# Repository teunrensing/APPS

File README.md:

# APPS

Dit is de repository met alle firmware- (source code), hardware- (kicad+schematische tekening) en GUI ontwerp bestanden (squareline studio) gemaakt door de S3 groep van 2022/2023.
De firmware is geschreven in c en maakt gebruik van het esp-idf framework. Esp-idf is een framework wat los geinstalleerd moet worden en niet meegeleverd wordt met een IDE.

VSCode in combinatie met de c/c++ en c/c++ extension pack is het makkelijkst op te zetten. Voor een handleiding [klik hier](https://github.com/teunrensing/APPS/tree/main/docs/install_vscode.md)
De hardware ontwerpbestanden zijn gemaakt in kicad, er staat nog een actuele PDF van de schematische tekening in de GitHub repo.

De GUI ontwerpbestanden zijn gemaakt in squareline studio. (Let op! In autogegenereerde .c bestanden van squareline studio wordt schaduw gebruikt. Dit onderdeel werkt niet en laat de ESP32 crashen. Verwijder deze stukjes code bij het porten van de code naar de ESP32.)

## Status Hardware
De hardware functioneert. Er zijn wat kleine foutjes. Zo zijn de ID_RES pullup weerstanden verkeerd getekend. En zijn niet alle modules precies zoals ze zouden moeten zijn.
Mocht iemand zin hebben om een volgende versie te maken... hier wat tips:
- Gebruik grotere onderdelen (geen mssop flipflop)
- Haal het flipflop flankdetectie circuit eruit voor de encoder
- Maak gebruik van een ESP32 devboard i.p.v. een esp32-wroom module
- Blijf gebruik maken van standaard onderdelen zoals: 74HC14 en 74HC595
- Haal de extra output en input pins weg. 
- Haal een hele boel switch input pins weg. 
- Haal de flat flex connector weg voor een display

## Status Software

Er zijn op dit moment drie volledige instelschermen (Licht, Vibratie en Tens) volledig af en functionerend. De code is nog vrij grof en lelijk. Dit kan flink gerefactord worden nog. 
- Er is een module driver voor licht en motor. **Maar de Tens driver ontbreekt nog.**
- Er is geen datacommunicatie protocol gemaakt voor externe communicatie met sensoren.
- Er is geen stuk software gemaakt die gebruik maakt van de microsd kaart slot.
- Er is geen stuk software die detecteert dat de noodstop is ingedrukt. Dit is op dit moment alleen in hardware afgehandeld.
- Er zijn geen unit testen (cmock of dut testen)

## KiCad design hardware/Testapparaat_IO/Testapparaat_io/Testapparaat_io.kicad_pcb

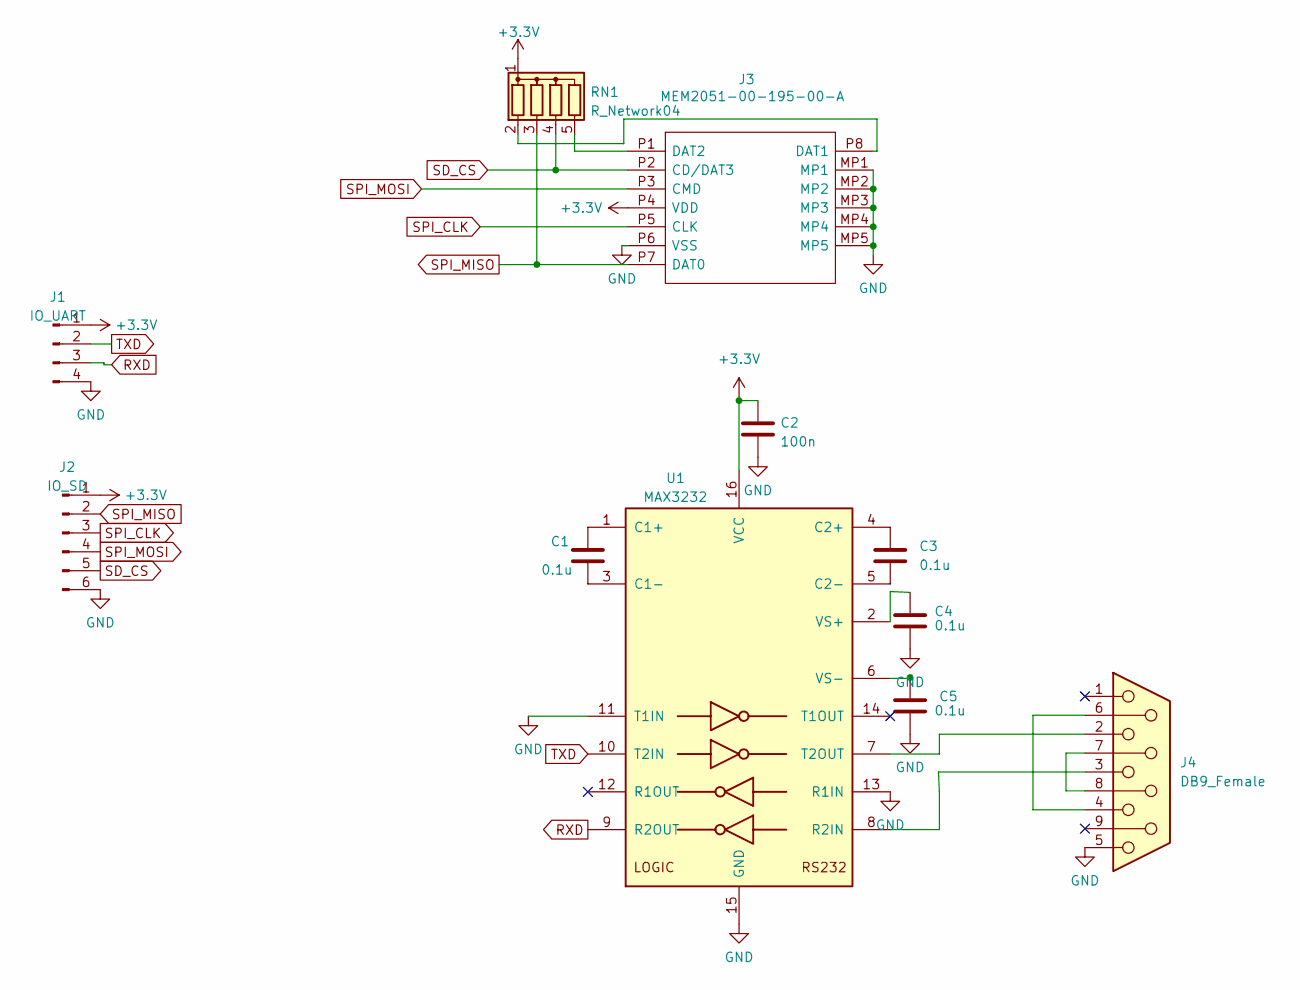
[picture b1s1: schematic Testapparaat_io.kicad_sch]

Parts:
C1, C3, C4, C5: 0.1u; C_0603_1608Metric_Pad1.08x0.95mm_HandSolder
C2: 100n; C_0603_1608Metric_Pad1.08x0.95mm_HandSolder
J1: IO_UART; PinHeader_1x04_P2.54mm_Horizontal
J2: IO_SD; PinHeader_1x06_P2.54mm_Horizontal
J3: MEM2051-00-195-00-A; MEM20510019500A; Manufacturer_Part_Number MEM2051-00-195-00-A; Mouser Part Number 640-MEM20510019500A
J4: DB9_Female; G17C0900132EU
RN1: R_Network04; R_Array_SIP5
U1: MAX3232; TSSOP-16_4.4x5mm_P0.65mm

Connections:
+3.3V: C2.1, J1.1, J2.1, J3.P4 (VDD), RN1.1 (common), U1.16 (VCC)
GND: C2.2, C4.1, C5.2, J1.4, J2.6, J3.MP1, J3.MP2, J3.MP3, J3.MP4, J3.MP5, J3.P6 (VSS), J4.5, U1.11 (T1IN), U1.13 (R1IN), U1.15 (GND)
unnamed: C1.1, U1.1 (C1+)
unnamed: C1.2, U1.3 (C1-)
unnamed: C3.1, U1.4 (C2+)
unnamed: C3.2, U1.5 (C2-)
unnamed: C4.2, U1.2 (VS+)
unnamed: C5.1, U1.6 (VS-)
unnamed: J3.P8 (DAT1), RN1.2 (R1)
unnamed: J4.2, U1.7 (T2OUT)
unnamed: J4.3, U1.8 (R2IN)
unnamed: J4.4, J4.6
unnamed: J4.7, J4.8
unnamed: J3.P1 (DAT2), RN1.5 (R4)
RXD: J1.3, U1.9 (R2OUT)
SD_CS: J2.5, J3.P2 (CD/DAT3), RN1.4 (R3)
SPI_CLK: J2.3, J3.P5 (CLK)
SPI_MISO: J2.2, J3.P7 (DAT0), RN1.3 (R2)
SPI_MOSI: J2.4, J3.P3 (CMD)
TXD: J1.2, U1.10 (T2IN)

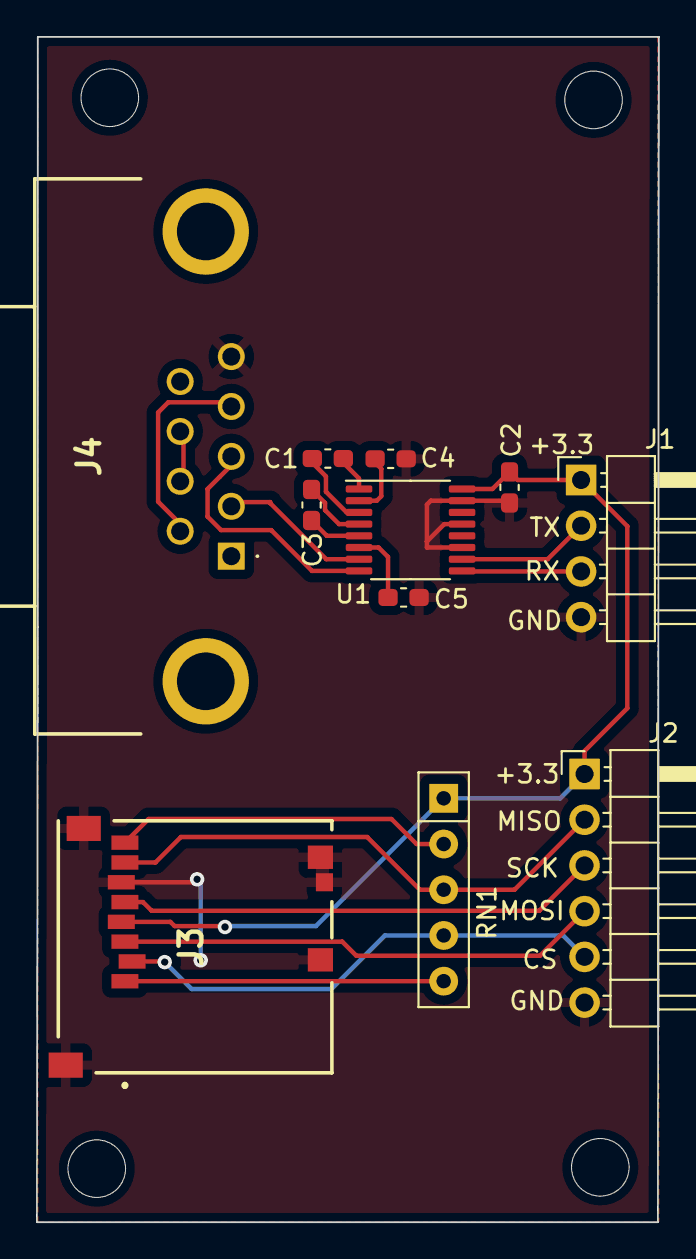
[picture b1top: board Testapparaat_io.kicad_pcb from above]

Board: 2 copper layers, 34.5 x 65.8 mm, 11 parts (0 on the bottom side), 20 nets.

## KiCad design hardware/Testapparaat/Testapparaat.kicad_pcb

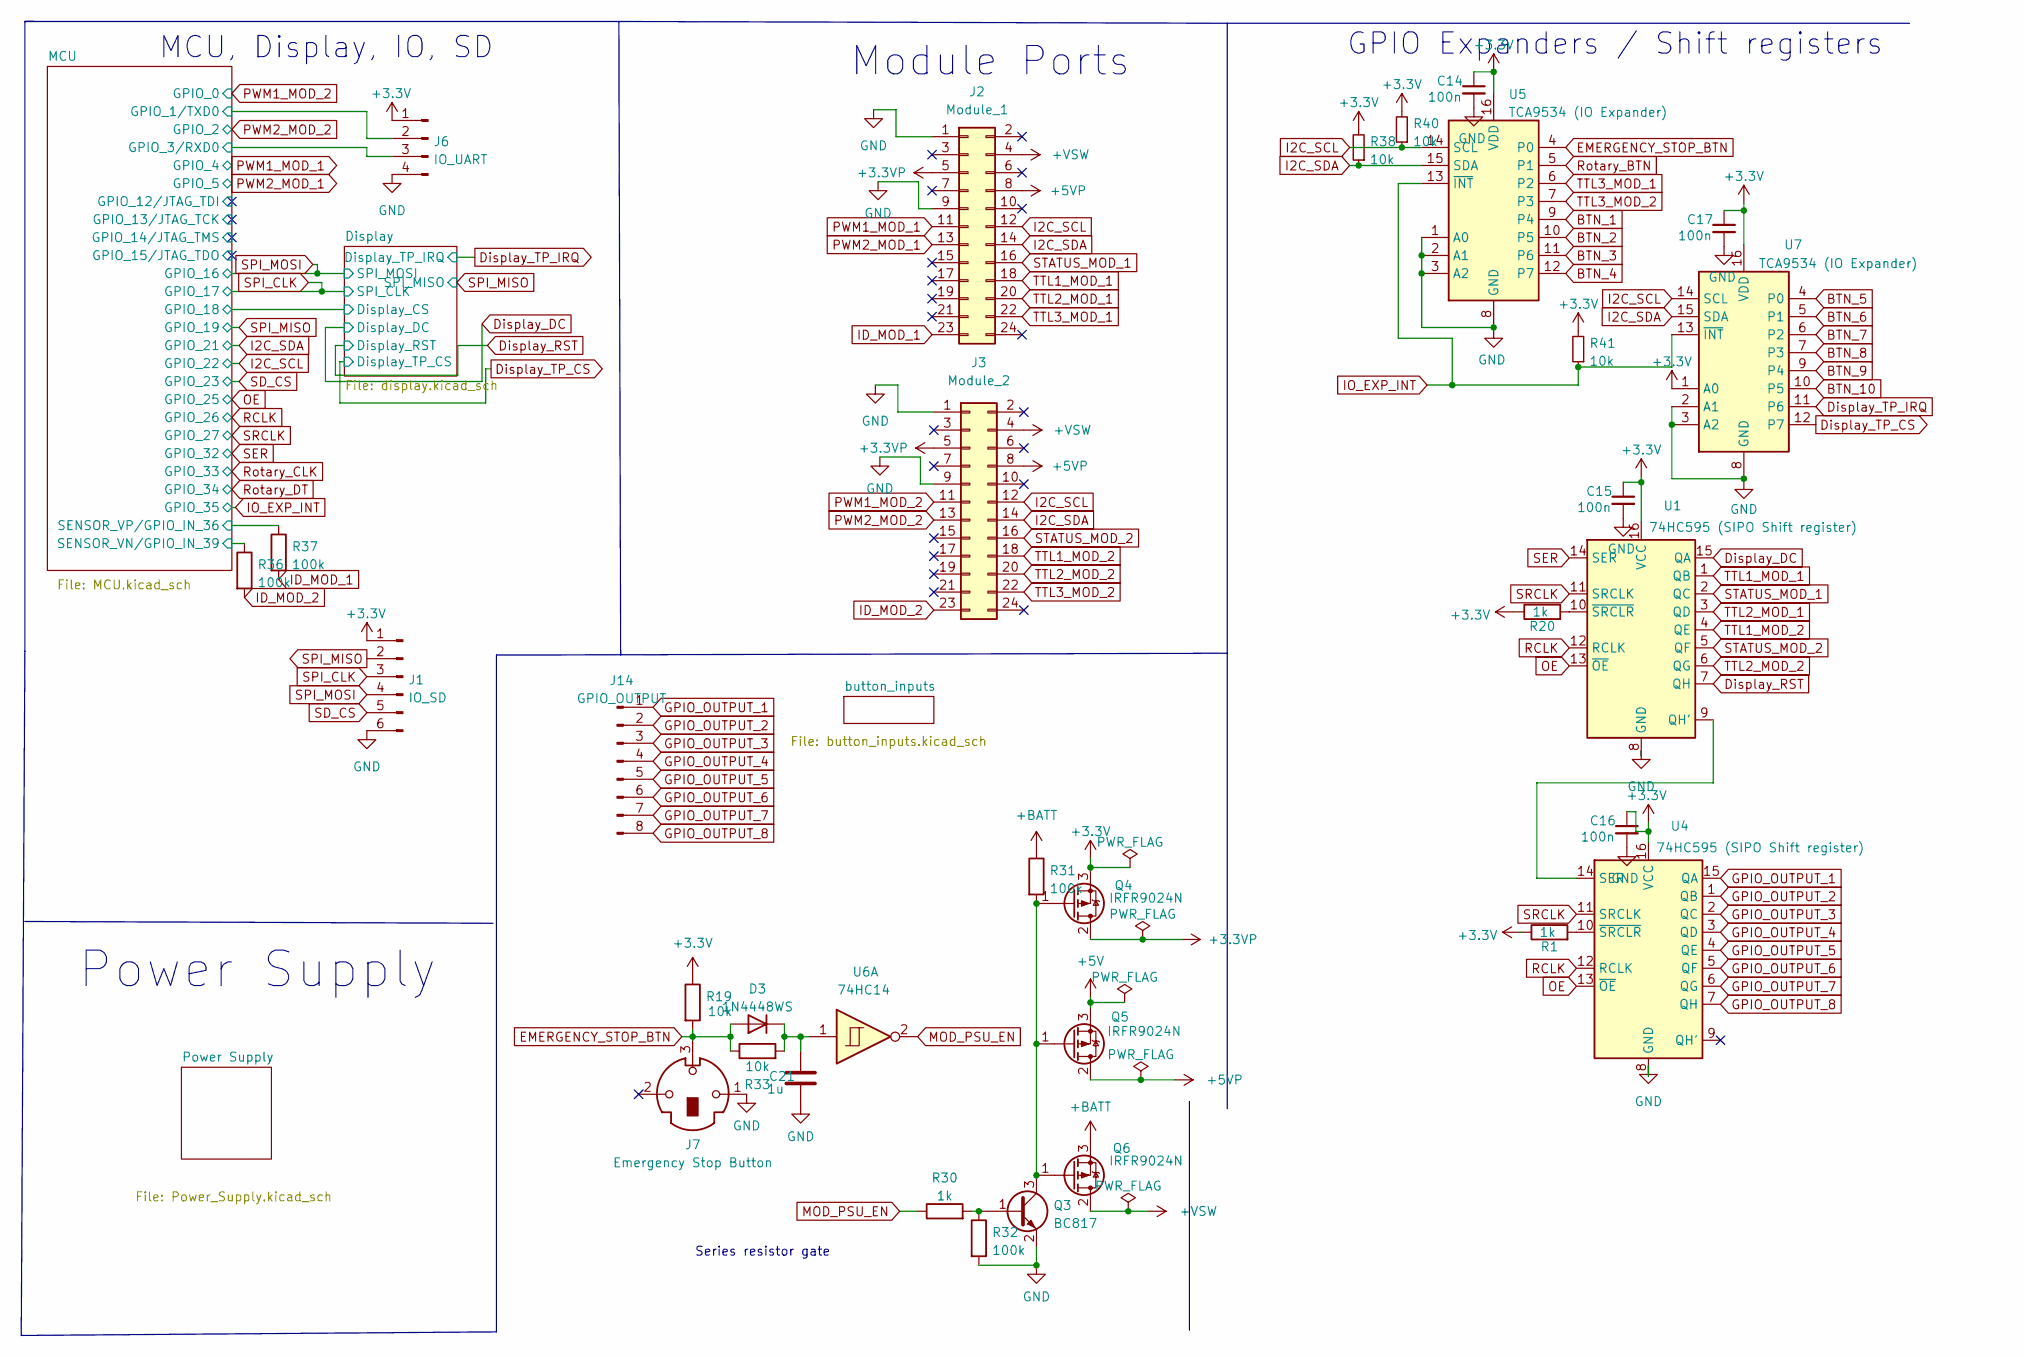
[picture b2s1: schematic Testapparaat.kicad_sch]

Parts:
C14, C15, C16, C17: 100n; C_0603_1608Metric_Pad1.08x0.95mm_HandSolder
C21: 1u; C_0603_1608Metric_Pad1.08x0.95mm_HandSolder
D3: 1N4448WS; D_SOD-323
J1: IO_SD; PinHeader_1x06_P2.54mm_Horizontal
J2: Module_1; PinHeader_2x12_P2.54mm_Horizontal
J3: Module_2; PinHeader_2x12_P2.54mm_Horizontal
J6: IO_UART; PinHeader_1x04_P2.54mm_Horizontal
J7: Emergency Stop Button; PinHeader_1x03_P2.54mm_Horizontal
J14: GPIO_OUTPUT; PinHeader_2x04_P2.54mm_Vertical_SMD
Q3: BC817; SOT-23
Q4, Q5, Q6: IRFR9024N; TO-252-3_TabPin2
R1, R20, R30: 1k; R_0603_1608Metric_Pad0.98x0.95mm_HandSolder
R19, R33, R38, R40, R41: 10k; R_0603_1608Metric_Pad0.98x0.95mm_HandSolder
R31, R32, R36, R37: 100k; R_0603_1608Metric_Pad0.98x0.95mm_HandSolder
U1, U4: 74HC595 (SIPO Shift register); 74HC595DQ100118
U5, U7: TCA9534 (IO Expander); SOP65P640X120-16N
U6: 74HC14; SO-14_3.9x8.65mm_P1.27mm

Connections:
+3.3V: C14.1, C15.1, C16.1, C17.1, J1.1, J6.1, Q4.3 (S), R1.1, R19.1, R20.1, R38.2, R40.2, R41.2, U1.16 (VCC), U4.16 (VCC), U5.16 (VDD), U7.1 (A0), U7.16 (VDD); also elsewhere on the board
+3.3VP: J2.5, J3.5, Q4.2 (D)
+5V: Q5.3 (S); also elsewhere on the board
+5VP: J2.8, J3.8, Q5.2 (D)
+BATT: Q6.3 (S), R31.1; also elsewhere on the board
+VSW: J2.4, J3.4, Q6.2 (D)
/MCU/GPIO_1/TXD0: J6.2; also elsewhere on the board
/MCU/GPIO_3/RXD0: J6.3; also elsewhere on the board
/MCU/SENSOR_VN/GPIO_IN_39: R36.1; also elsewhere on the board
/MCU/SENSOR_VP/GPIO_IN_36: R37.1; also elsewhere on the board
BTN_1: U5.9 (P4); also elsewhere on the board
BTN_2: U5.10 (P5); also elsewhere on the board
BTN_3: U5.11 (P6); also elsewhere on the board
BTN_4: U5.12 (P7); also elsewhere on the board
BTN_5: U7.4 (P0); also elsewhere on the board
BTN_6: U7.5 (P1); also elsewhere on the board
BTN_7: U7.6 (P2); also elsewhere on the board
BTN_8: U7.7 (P3); also elsewhere on the board
BTN_9: U7.9 (P4); also elsewhere on the board
BTN_10: U7.10 (P5); also elsewhere on the board
Display_DC: U1.15 (QA); also elsewhere on the board
Display_RST: U1.7 (QH); also elsewhere on the board
Display_TP_CS: U7.12 (P7); also elsewhere on the board
Display_TP_IRQ: U7.11 (P6); also elsewhere on the board
EMERGENCY_STOP_BTN: D3.2 (A), J7.3, R19.2, R33.1, U5.4 (P0)
GPIO_OUTPUT_1: J14.1, U4.15 (QA)
GPIO_OUTPUT_2: J14.2, U4.1 (QB)
GPIO_OUTPUT_3: J14.3, U4.2 (QC)
GPIO_OUTPUT_4: J14.4, U4.3 (QD)
GPIO_OUTPUT_5: J14.5, U4.4 (QE)
GPIO_OUTPUT_6: J14.6, U4.5 (QF)
GPIO_OUTPUT_7: J14.7, U4.6 (QG)
GPIO_OUTPUT_8: J14.8, U4.7 (QH)
I2C_SCL: J2.12, J3.12, R40.1, U5.14 (SCL), U7.14 (SCL); also elsewhere on the board
I2C_SDA: J2.14, J3.14, R38.1, U5.15 (SDA), U7.15 (SDA); also elsewhere on the board
ID_MOD_1: J2.23, R37.2
ID_MOD_2: J3.23, R36.2
IO_EXP_INT: R41.1, U5.13 (~INT), U7.13 (~INT); also elsewhere on the board
MOD_PSU_EN: R30.1, U6.2
unnamed: C21.1, D3.1 (K), R33.2, U6.1
unnamed: Q3.1 (B), R30.2, R32.1
unnamed: Q3.3 (C), Q4.1 (G), Q5.1 (G), Q6.1 (G), R31.2
unnamed: R1.2, U4.10 (~SRCLR)
unnamed: R20.2, U1.10 (~SRCLR)
unnamed: U1.9 (QH'), U4.14 (SER)
OE: U1.13 (~OE), U4.13 (~OE); also elsewhere on the board
PWM1_MOD_1: J2.11; also elsewhere on the board
PWM1_MOD_2: J3.11; also elsewhere on the board
PWM2_MOD_1: J2.13; also elsewhere on the board
PWM2_MOD_2: J3.13; also elsewhere on the board
RCLK: U1.12 (RCLK), U4.12 (RCLK); also elsewhere on the board
Rotary_BTN: U5.5 (P1); also elsewhere on the board
SD_CS: J1.5; also elsewhere on the board
SER: U1.14 (SER); also elsewhere on the board
SPI_CLK: J1.3; also elsewhere on the board
SPI_MISO: J1.2; also elsewhere on the board
SPI_MOSI: J1.4; also elsewhere on the board
SRCLK: U1.11 (SRCLK), U4.11 (SRCLK); also elsewhere on the board
STATUS_MOD_1: J2.16, U1.2 (QC)
STATUS_MOD_2: J3.16, U1.5 (QF)
TTL1_MOD_1: J2.18, U1.1 (QB)
TTL1_MOD_2: J3.18, U1.4 (QE)
TTL2_MOD_1: J2.20, U1.3 (QD)
TTL2_MOD_2: J3.20, U1.6 (QG)
TTL3_MOD_1: J2.22, U5.6 (P2)
TTL3_MOD_2: J3.22, U5.7 (P3)

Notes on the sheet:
MCU, Display, IO, SD
Series resistor gate
GPIO Expanders / Shift registers
Power Supply
Module Ports

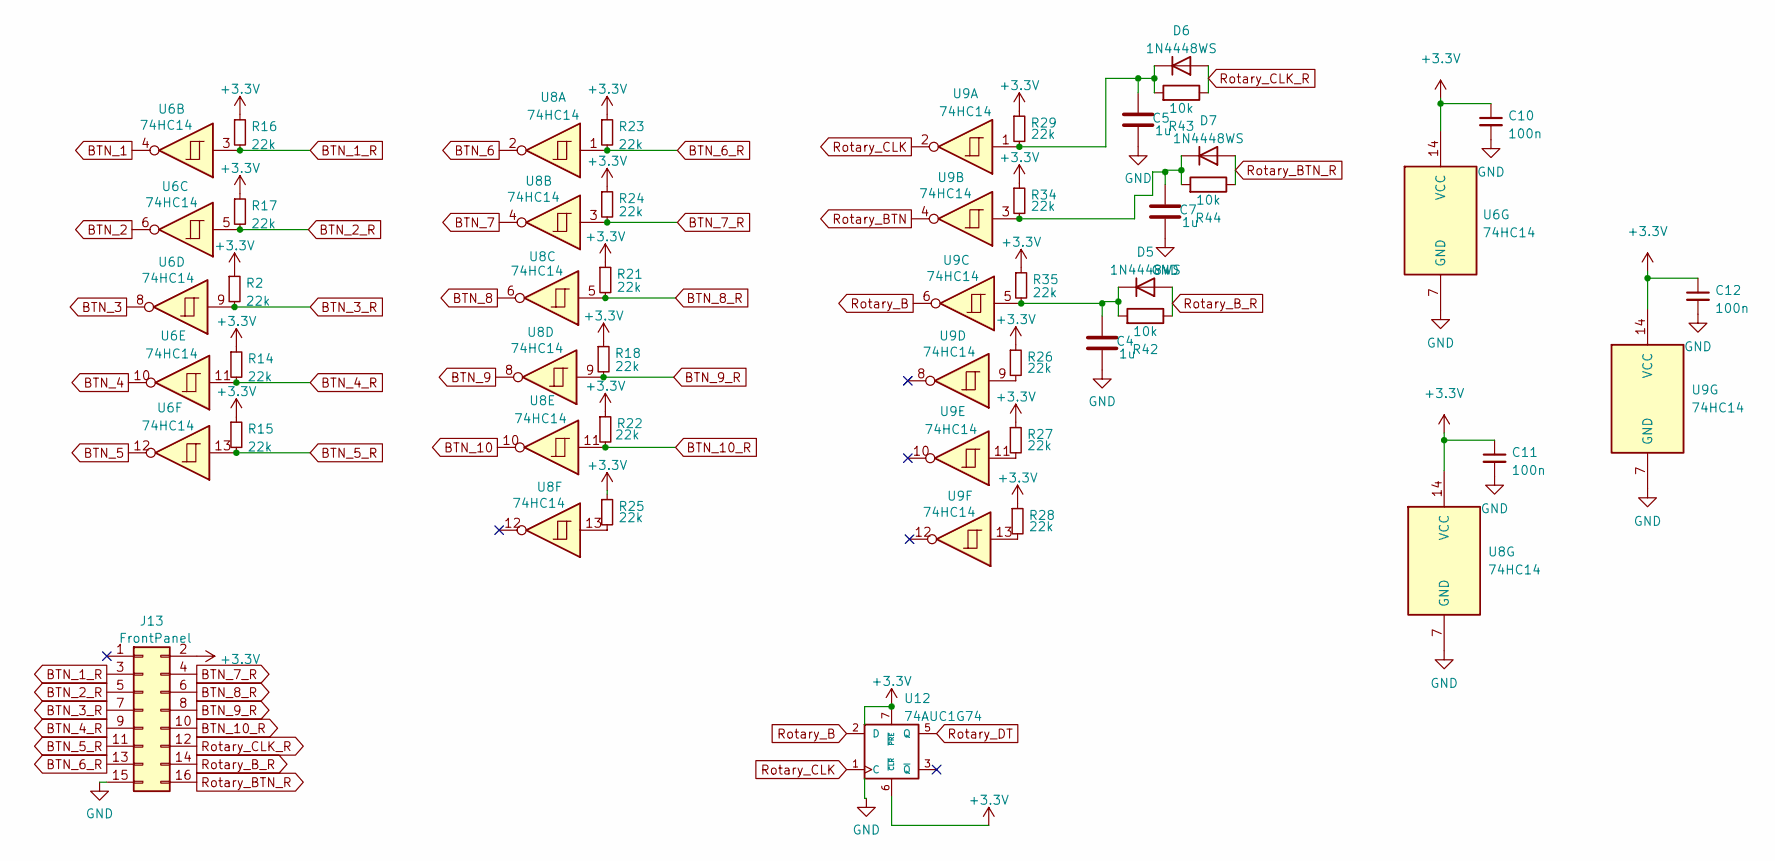
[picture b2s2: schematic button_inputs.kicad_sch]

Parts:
C4, C5, C7: 1u; C_0603_1608Metric_Pad1.08x0.95mm_HandSolder
C10, C11, C12: 100n; C_0603_1608Metric_Pad1.08x0.95mm_HandSolder
D5, D6, D7: 1N4448WS; D_SOD-323
J13: FrontPanel; PinHeader_2x08_P2.54mm_Vertical_SMD
R2, R14, R15, R16, R17, R18, R21, R22, R23, R24, R25, R26, R27, R28, R29, R34, R35: 22k; R_0603_1608Metric_Pad0.98x0.95mm_HandSolder
R42, R43, R44: 10k; R_0603_1608Metric_Pad0.98x0.95mm_HandSolder
U6, U8, U9: 74HC14; SO-14_3.9x8.65mm_P1.27mm
U12: 74AUC1G74; VSSOP-8_2.3x2mm_P0.5mm

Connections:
+3.3V: C10.1, C11.1, C12.1, J13.2, R2.1, R14.1, R15.1, R16.1, R17.1, R18.1, R21.1, R22.1, R23.1, R24.1, R25.1, R26.1, R27.1, R28.1, R29.1, R34.1, R35.1, U6.14 (VCC), U8.14 (VCC), U9.14 (VCC), U12.6 (~CLR), U12.7 (~PRE), U12.8 (VCC); also elsewhere on the board
BTN_1: U6.4; also elsewhere on the board
BTN_1_R: J13.3, R16.2, U6.3
BTN_2: U6.6; also elsewhere on the board
BTN_2_R: J13.5, R17.2, U6.5
BTN_3: U6.8; also elsewhere on the board
BTN_3_R: J13.7, R2.2, U6.9
BTN_4: U6.10; also elsewhere on the board
BTN_4_R: J13.9, R14.2, U6.11
BTN_5: U6.12; also elsewhere on the board
BTN_5_R: J13.11, R15.2, U6.13
BTN_6: U8.2; also elsewhere on the board
BTN_6_R: J13.13, R23.2, U8.1
BTN_7: U8.4; also elsewhere on the board
BTN_7_R: J13.4, R24.2, U8.3
BTN_8: U8.6; also elsewhere on the board
BTN_8_R: J13.6, R21.2, U8.5
BTN_9: U8.8; also elsewhere on the board
BTN_9_R: J13.8, R18.2, U8.9
BTN_10: U8.10; also elsewhere on the board
BTN_10_R: J13.10, R22.2, U8.11
unnamed: C4.1, D5.1 (K), R35.2, R42.2, U9.5
unnamed: C5.1, D6.1 (K), R29.2, R43.2, U9.1
unnamed: C7.1, D7.1 (K), R34.2, R44.2, U9.3
unnamed: R25.2, U8.13
unnamed: R26.2, U9.9
unnamed: R27.2, U9.11
unnamed: R28.2, U9.13
Rotary_B: U9.6, U12.2 (D)
Rotary_BTN: U9.4; also elsewhere on the board
Rotary_BTN_R: D7.2 (A), J13.16, R44.1
Rotary_B_R: D5.2 (A), J13.14, R42.1
Rotary_CLK: U9.2, U12.1 (C); also elsewhere on the board
Rotary_CLK_R: D6.2 (A), J13.12, R43.1
Rotary_DT: U12.5 (Q); also elsewhere on the board

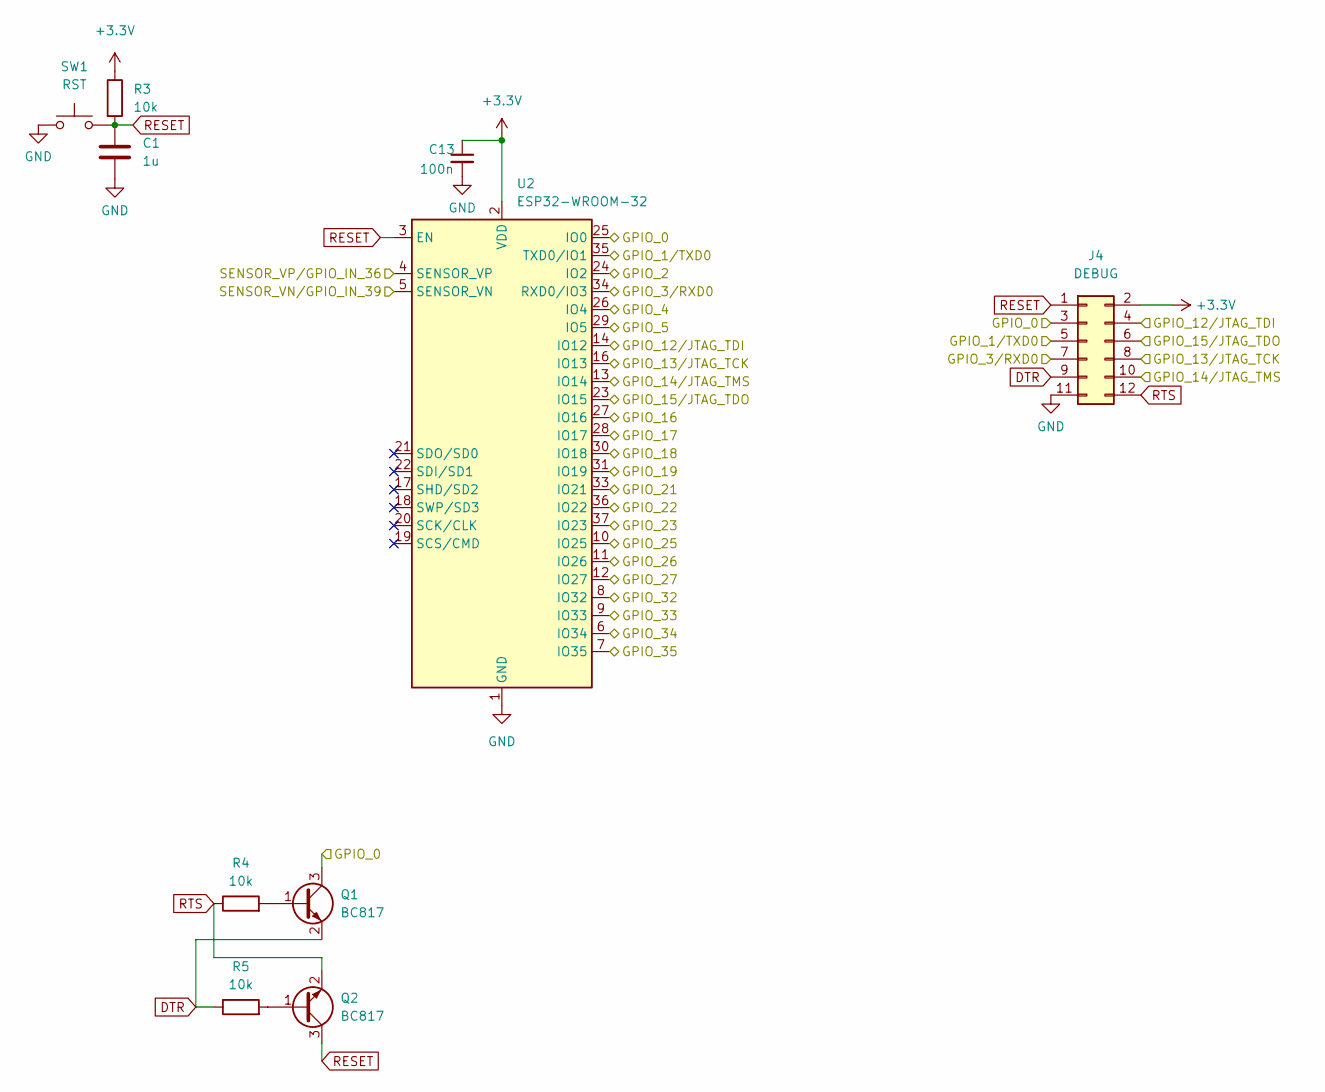
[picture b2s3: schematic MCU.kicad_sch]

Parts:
C1: 1u; C_0603_1608Metric_Pad1.08x0.95mm_HandSolder
C13: 100n; C_0603_1608Metric_Pad1.08x0.95mm_HandSolder
J4: DEBUG; PinHeader_2x06_P2.54mm_Vertical_SMD
Q1, Q2: BC817; SOT-23
R3, R4, R5: 10k; R_0603_1608Metric_Pad0.98x0.95mm_HandSolder
SW1: RST; SW_SPST_B3S-1000
U2: ESP32-WROOM-32

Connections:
+3.3V: C13.1, J4.2, R3.1, U2.2 (VDD); also elsewhere on the board
/Display/Display_CS: U2.30 (IO18); also elsewhere on the board
/MCU/GPIO_1/TXD0: J4.5, U2.35 (TXD0/IO1); also elsewhere on the board
/MCU/GPIO_3/RXD0: J4.7, U2.34 (RXD0/IO3); also elsewhere on the board
/MCU/GPIO_12/JTAG_TDI: J4.4, U2.14 (IO12)
/MCU/GPIO_13/JTAG_TCK: J4.8, U2.16 (IO13)
/MCU/GPIO_14/JTAG_TMS: J4.10, U2.13 (IO14)
/MCU/GPIO_15/JTAG_TDO: J4.6, U2.23 (IO15)
/MCU/SENSOR_VN/GPIO_IN_39: U2.5 (SENSOR_VN); also elsewhere on the board
/MCU/SENSOR_VP/GPIO_IN_36: U2.4 (SENSOR_VP); also elsewhere on the board
DTR: J4.9, Q1.2 (E), R5.1
I2C_SCL: U2.36 (IO22); also elsewhere on the board
I2C_SDA: U2.33 (IO21); also elsewhere on the board
IO_EXP_INT: U2.7 (IO35); also elsewhere on the board
unnamed: Q1.1 (B), R4.2
unnamed: Q2.1 (B), R5.2
OE: U2.10 (IO25); also elsewhere on the board
PWM1_MOD_1: U2.26 (IO4); also elsewhere on the board
PWM1_MOD_2: J4.3, Q1.3 (C), U2.25 (IO0); also elsewhere on the board
PWM2_MOD_1: U2.29 (IO5); also elsewhere on the board
PWM2_MOD_2: U2.24 (IO2); also elsewhere on the board
RCLK: U2.11 (IO26); also elsewhere on the board
RESET: C1.1, J4.1, Q2.3 (C), R3.2, SW1.2, U2.3 (EN)
RTS: J4.12, Q2.2 (E), R4.1
Rotary_CLK: U2.9 (IO33); also elsewhere on the board
Rotary_DT: U2.6 (IO34); also elsewhere on the board
SD_CS: U2.37 (IO23); also elsewhere on the board
SER: U2.8 (IO32); also elsewhere on the board
SPI_CLK: U2.28 (IO17); also elsewhere on the board
SPI_MISO: U2.31 (IO19); also elsewhere on the board
SPI_MOSI: U2.27 (IO16); also elsewhere on the board
SRCLK: U2.12 (IO27); also elsewhere on the board

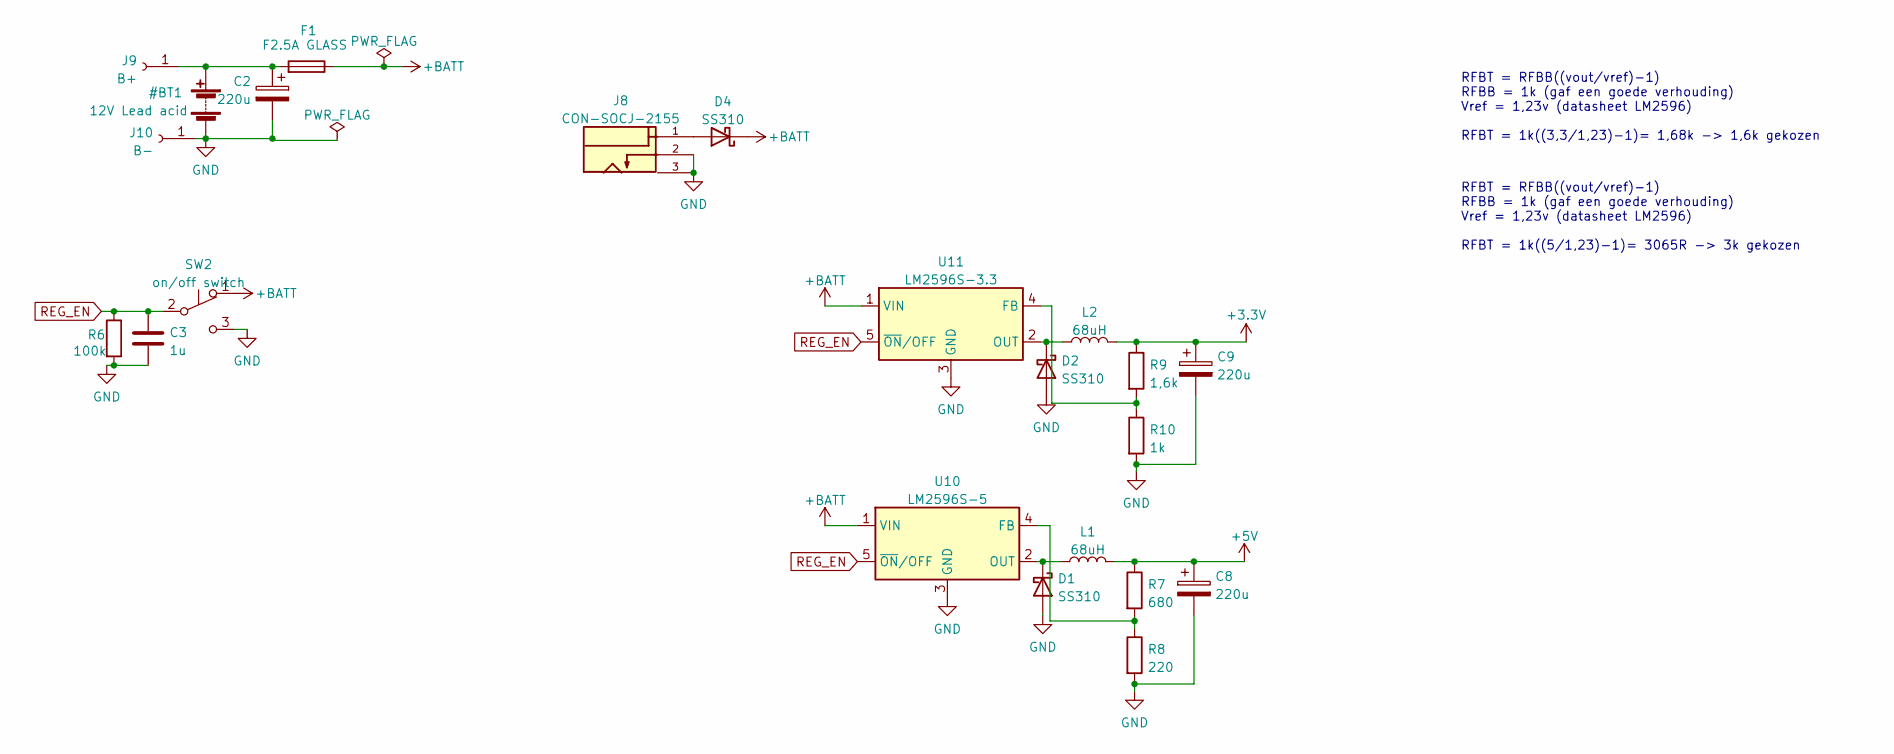
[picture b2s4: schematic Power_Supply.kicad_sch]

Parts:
C2, C8, C9: 220u; C_Radial_D10.0mm_H12.5mm_P5.00mm
C3: 1u; C_0603_1608Metric_Pad1.08x0.95mm_HandSolder
D1, D2, D4: SS310; D_SMA_Handsoldering
F1: F2.5A GLASS; Fuseholder_Littelfuse_100_series_5x20mm
J8: CON-SOCJ-2155; GRAVITECH_CON-SOCJ-2155; PARTREV NA
J9: B+; TestPoint_Plated_Hole_D2.0mm
J10: B-; TestPoint_Plated_Hole_D2.0mm
L1, L2: 68uH; L_Bourns_SRR1260
R6: 100k; R_0603_1608Metric_Pad0.98x0.95mm_HandSolder
R7: 680; R_0603_1608Metric_Pad0.98x0.95mm_HandSolder
R8: 220; R_0603_1608Metric_Pad0.98x0.95mm_HandSolder
R9: 1,6k; R_0603_1608Metric_Pad0.98x0.95mm_HandSolder
R10: 1k; R_0603_1608Metric_Pad0.98x0.95mm_HandSolder
SW2: on/off switch; SW_Slide_1P2T_CK_OS102011MS2Q
U10: LM2596S-5; TO-263-5_TabPin3
U11: LM2596S-3.3; TO-263-5_TabPin3

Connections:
+3.3V: C9.1, L2.2, R9.1; also elsewhere on the board
+5V: C8.1, L1.2, R7.1; also elsewhere on the board
+BATT: D4.1 (K), F1.1, SW2.1 (A), U10.1 (VIN), U11.1 (VIN); also elsewhere on the board
unnamed: D1.1 (K), L1.1, U10.2 (OUT)
unnamed: D2.1 (K), L2.1, U11.2 (OUT)
unnamed: D4.2 (A), J8.1
unnamed: R7.2, R8.1, U10.4 (FB)
unnamed: R9.2, R10.1, U11.4 (FB)
REG_EN: C3.1, R6.1, SW2.2 (B), U10.5 (~ON/OFF), U11.5 (~ON/OFF)

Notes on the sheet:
RFBT = RFBB((vout/vref)-1) RFBB = 1k (gaf een goede verhouding) Vref = 1,23v (datasheet LM2596) RFBT = 1k((5/1,23)-1)= 3065R -> 3k gekozen
RFBT = RFBB((vout/vref)-1) RFBB = 1k (gaf een goede verhouding) Vref = 1,23v (datasheet LM2596) RFBT = 1k((3,3/1,23)-1)= 1,68k -> 1,6k gekozen

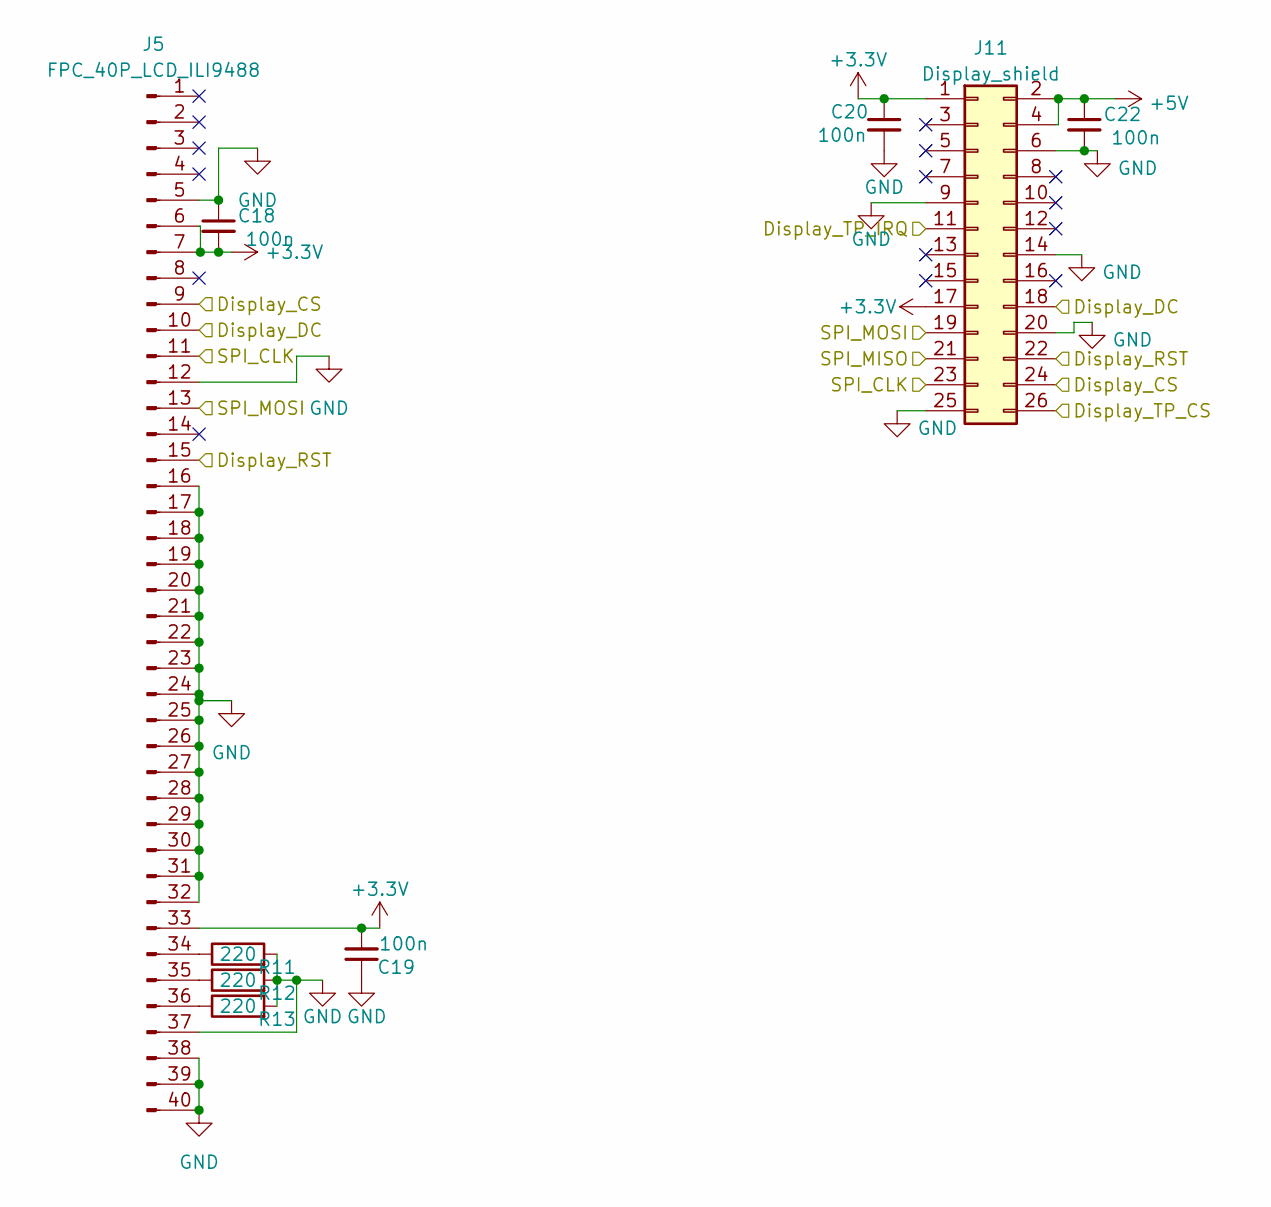
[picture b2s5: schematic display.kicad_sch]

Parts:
C18, C19, C20, C22: 100n; C_0603_1608Metric_Pad1.08x0.95mm_HandSolder
J5: FPC_40P_LCD_ILI9488; TE_4-1734839-0_1x40-1MP_P0.5mm_Horizontal
J11: Display_shield; PinHeader_2x13_P2.54mm_Vertical_SMD
R11, R12, R13: 220; R_0603_1608Metric_Pad0.98x0.95mm_HandSolder

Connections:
+3.3V: C18.2, C19.2, C20.1, J5.6, J5.7, J5.33, J11.1, J11.17; also elsewhere on the board
+5V: C22.1, J11.2, J11.4; also elsewhere on the board
/Display/Display_CS: J5.9, J11.24; also elsewhere on the board
Display_DC: J5.10, J11.18; also elsewhere on the board
Display_RST: J5.15, J11.22; also elsewhere on the board
Display_TP_CS: J11.26; also elsewhere on the board
Display_TP_IRQ: J11.11; also elsewhere on the board
unnamed: J5.34, R11.1
unnamed: J5.35, R12.1
unnamed: J5.36, R13.1
SPI_CLK: J5.11, J11.23; also elsewhere on the board
SPI_MISO: J11.21; also elsewhere on the board
SPI_MOSI: J5.13, J11.19; also elsewhere on the board

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
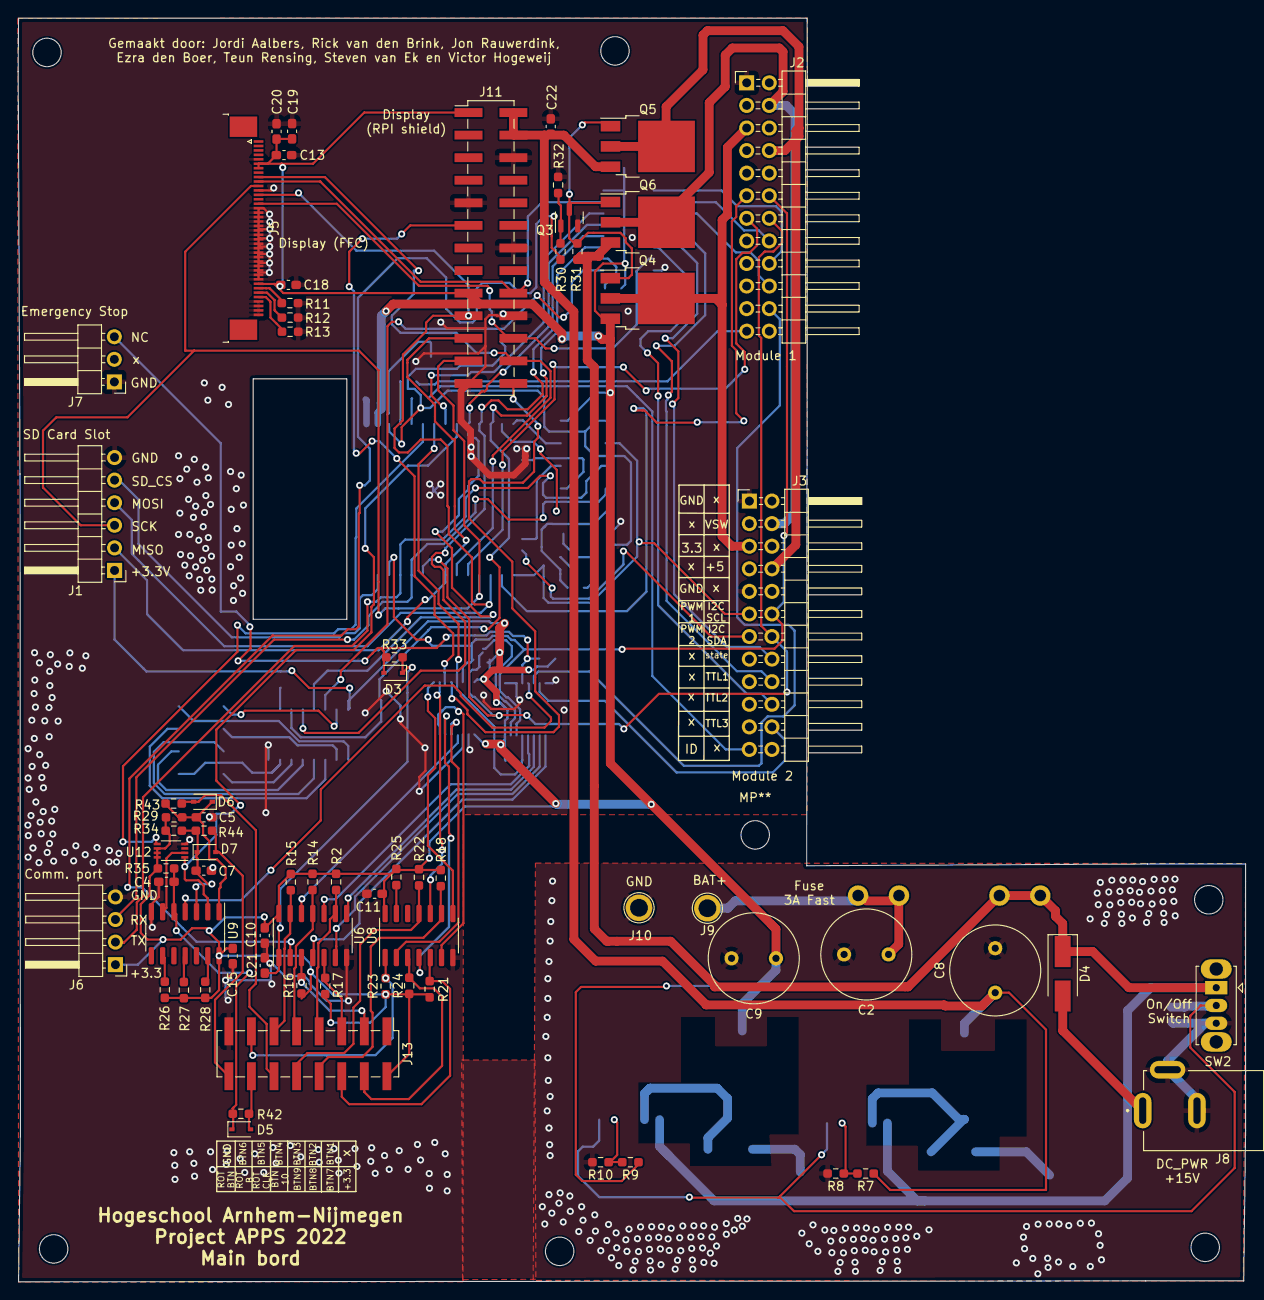
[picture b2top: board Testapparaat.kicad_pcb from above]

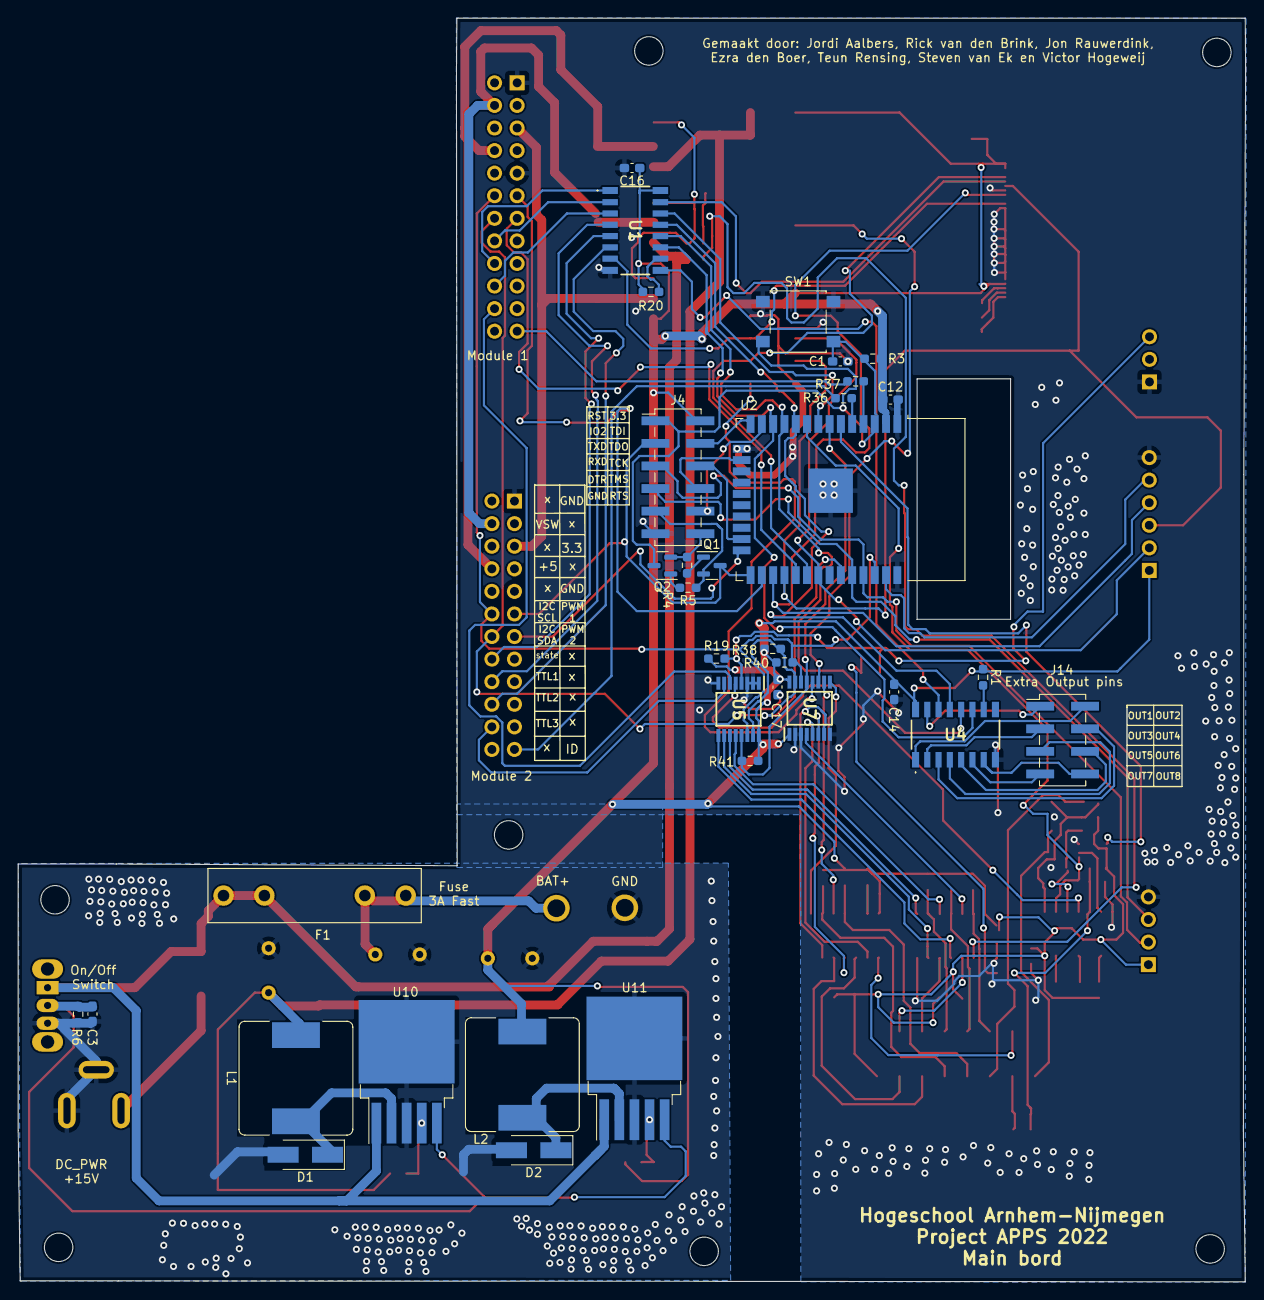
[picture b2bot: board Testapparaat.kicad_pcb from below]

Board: 2 copper layers, 138.1 x 142.2 mm, 107 parts (35 on the bottom side), 110 nets.

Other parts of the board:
MP**: MountingHole_3.2mm_M3

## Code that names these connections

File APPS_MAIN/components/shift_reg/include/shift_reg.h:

#ifndef SHIFT_REG_H
#define SHIFT_REG_H

#include <stdio.h>
#include "driver/gpio.h"

#define SR_LENGTH 8
#define HIGH 1
#define LOW 0
#define SHIFT_MASK(x) (1ULL << x)
#define PBM_SR_CONFIG(w, x, y, z) (SHIFT_MASK(w) | SHIFT_MASK(x) | SHIFT_MASK(y) | SHIFT_MASK(z))

typedef struct
{

    char get[SR_LENGTH];

} shift_reg_state;

typedef struct
{
    gpio_num_t OE,
        RCLK,
        SER,
        SRCLK;

} shift_register_pins;

typedef struct
{
    shift_register_pins sr_pins;
    gpio_config_t io_config;
    shift_reg_state sr_state;

} shift_register;

// set the pins of the shift register
void set_pins_shift_register(shift_register *config, gpio_num_t OE, gpio_num_t RCLK, gpio_num_t SER, gpio_num_t SRCLK);
// config a shift register
void config_shift_register(shift_register config);
// shift register memory update
void shift_register_update_memory(shift_register sr_config);
// shift register set what is in the memory of the shift register to the output
void shift_register_update_output(shift_register sr_config);
// set a pin high or low based on the position, value and which shift shift register
void shift_register_set(int position, char value, shift_register *config);
// set all low
void shift_register_setup(shift_register *config);
// Set a shift register in series
void set_pins_serie_shift_register(shift_register config1, shift_register *config2);
// combining 2 shift registers in series set function
void shift_register_com_update_memory(shift_register config1, shift_register config2);
#endif
